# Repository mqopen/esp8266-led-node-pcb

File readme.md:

# ESP8266 LED Node PCB

## Features

 - Powered by mini DC-DC power supply module ([LM2596](http://www.ti.com/lit/ds/symlink/lm2596.pdf) chip).
 - 5.5 mm center positive jack.
 - On-board programming connector.
 - Programming push button.
 - Jumper for enabling power supply module.
 - Notification LED.
 - Intended to be manufactured by [dirtypcbs.com](http://dirtypcbs.com/).
 - AVR like ISP header for in circuit programming.
 - MOSFET transistor. 
 - RJ-11 connector for connecting LED strips.

## Images

## Get board

You can order PCB on this [link](http://dirtypcbs.com/store/designer/details/9988/967/esp8266-led-v0-1-0-zip).

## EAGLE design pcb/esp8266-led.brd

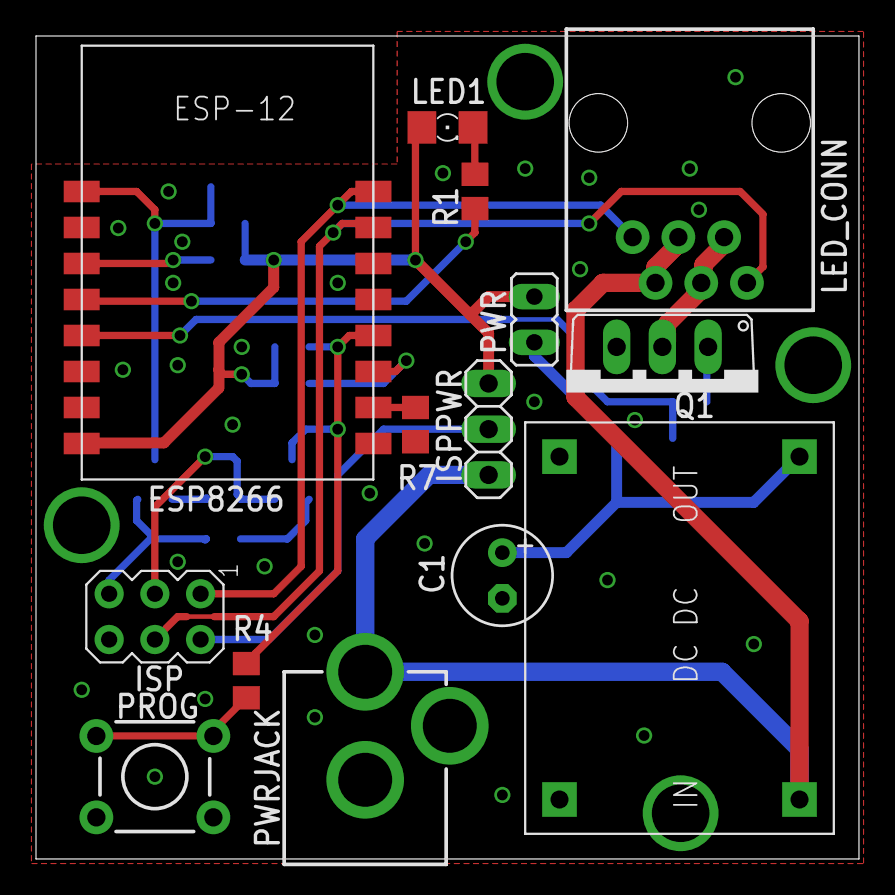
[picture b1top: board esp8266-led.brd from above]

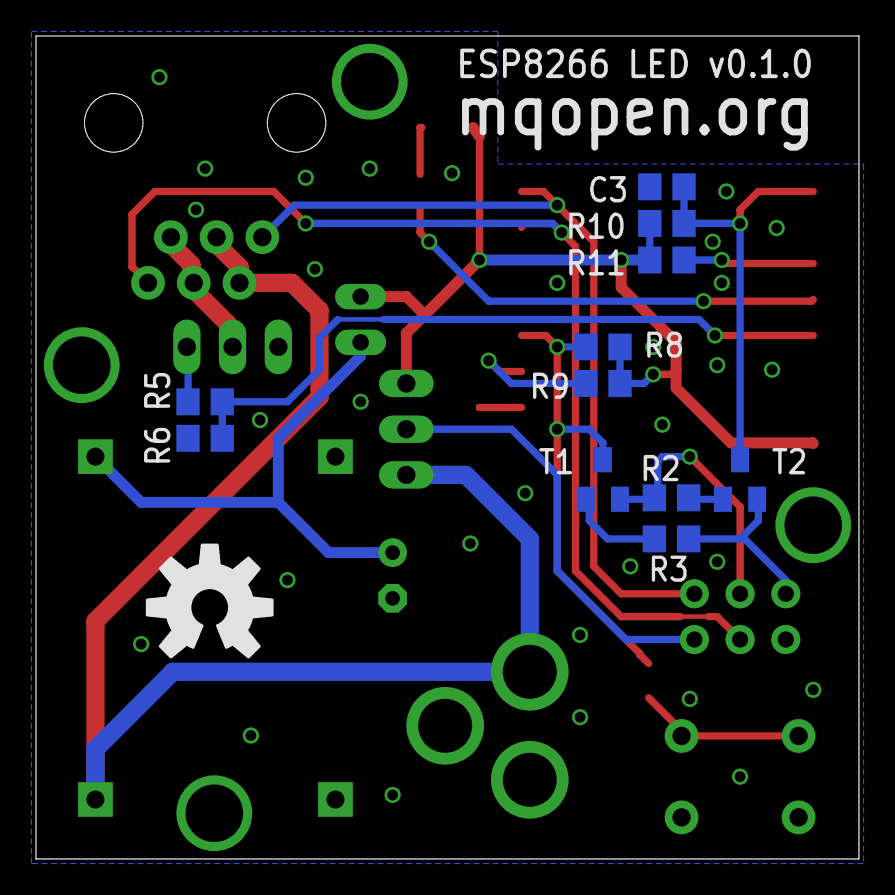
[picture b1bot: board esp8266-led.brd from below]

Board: 2 copper layers, 45.7 x 45.7 mm, 26 parts (12 on the bottom side), 22 nets.

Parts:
C1: 220uF; E2,5-6
C3: 100nF; C0805
ESP8266: ESP8266_ESP-12; ESP8266-ESP12
ISP: AVRISP-6; AVRISP
ISPPWR: 1X03
LED1: RED; 1206
LED_CONN: RJ11; RJ11-6
PROG: TACTILE-PTH
PWR: JP1
PWRJACK: POWER_JACKPTH; POWER_JACK_PTH
Q1: TO220V
R1: 82R; R0805
R2, R3, R7, R8, R9, R10, R11: 12K; R0805
R4: 470R; R0805
R5: 120R; R0805
R6: 120K; R0805
T1, T2: SOT23-BEC
U$1: OSHW-LOGOL; OSHW-LOGO-L
U$2: DC-DC-SMALL; DC-DC

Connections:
+3V3: ESP8266.16, ISPPWR.1, LED1.A, PWR.2, R8.2, R9.2, R10.2, R11.2
+12V: ISPPWR.3, LED_CONN.4, LED_CONN.5, PWRJACK.PWR, U$2.P$1
DTR: ISP.3, R2.2, T1.E
EN: ESP8266.11, R11.1
GND: C1.-, C3.1, ESP8266.1, ISP.6, PROG.3, PROG.4, PWRJACK.GND, PWRJACK.GNDBREAK, Q1.3, R6.2, R7.2, U$2.P$3, U$2.P$4
GPIO0: ESP8266.4, R4.1, R8.1, T1.C
GPIO2: ESP8266.3, R9.1
GPIO14: ESP8266.13, R5.1, R6.1
GPIO16: ESP8266.12, R1.2
unnamed: LED1.C, R1.1
unnamed: C1.+, PWR.1, U$2.P$2
unnamed: R2.1, T2.B
unnamed: PROG.1, PROG.2, R4.2
unnamed: ESP8266.2, R7.1
unnamed: ISP.2, ISPPWR.2
unnamed: R3.1, T1.B
unnamed: Q1.1, R5.2
unnamed: LED_CONN.2, LED_CONN.3, Q1.2
NRST: C3.2, ESP8266.9, R10.1, T2.C
RST: ISP.5, R3.2, T2.E
RXD: ESP8266.7, ISP.4, LED_CONN.1
TXD: ESP8266.8, ISP.1, LED_CONN.6

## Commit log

2016-06-14 Initial commit.
2016-06-14 Created basic readme.
2016-06-14 Updated gitignore.
2016-06-14 Updated MOSFET dersistor values.
2016-12-12 Added board image.
2016-12-12 Added gerber files.
2016-12-12 Added schematics file.
2016-12-12 Added images.
2016-12-12 Added changelog.
2016-12-12 Updated changelog.
2016-12-12 Added order link.

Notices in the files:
parts and their libraries:
SparkFun-Connectors: Licensing: Creative Commons ShareAlike 4.0 International - https://creativecommons.org/licenses/by-sa/4.0
SparkFun: Licensing: CC v3.0 Share-Alike You are welcome to use this library for commercial purposes.
